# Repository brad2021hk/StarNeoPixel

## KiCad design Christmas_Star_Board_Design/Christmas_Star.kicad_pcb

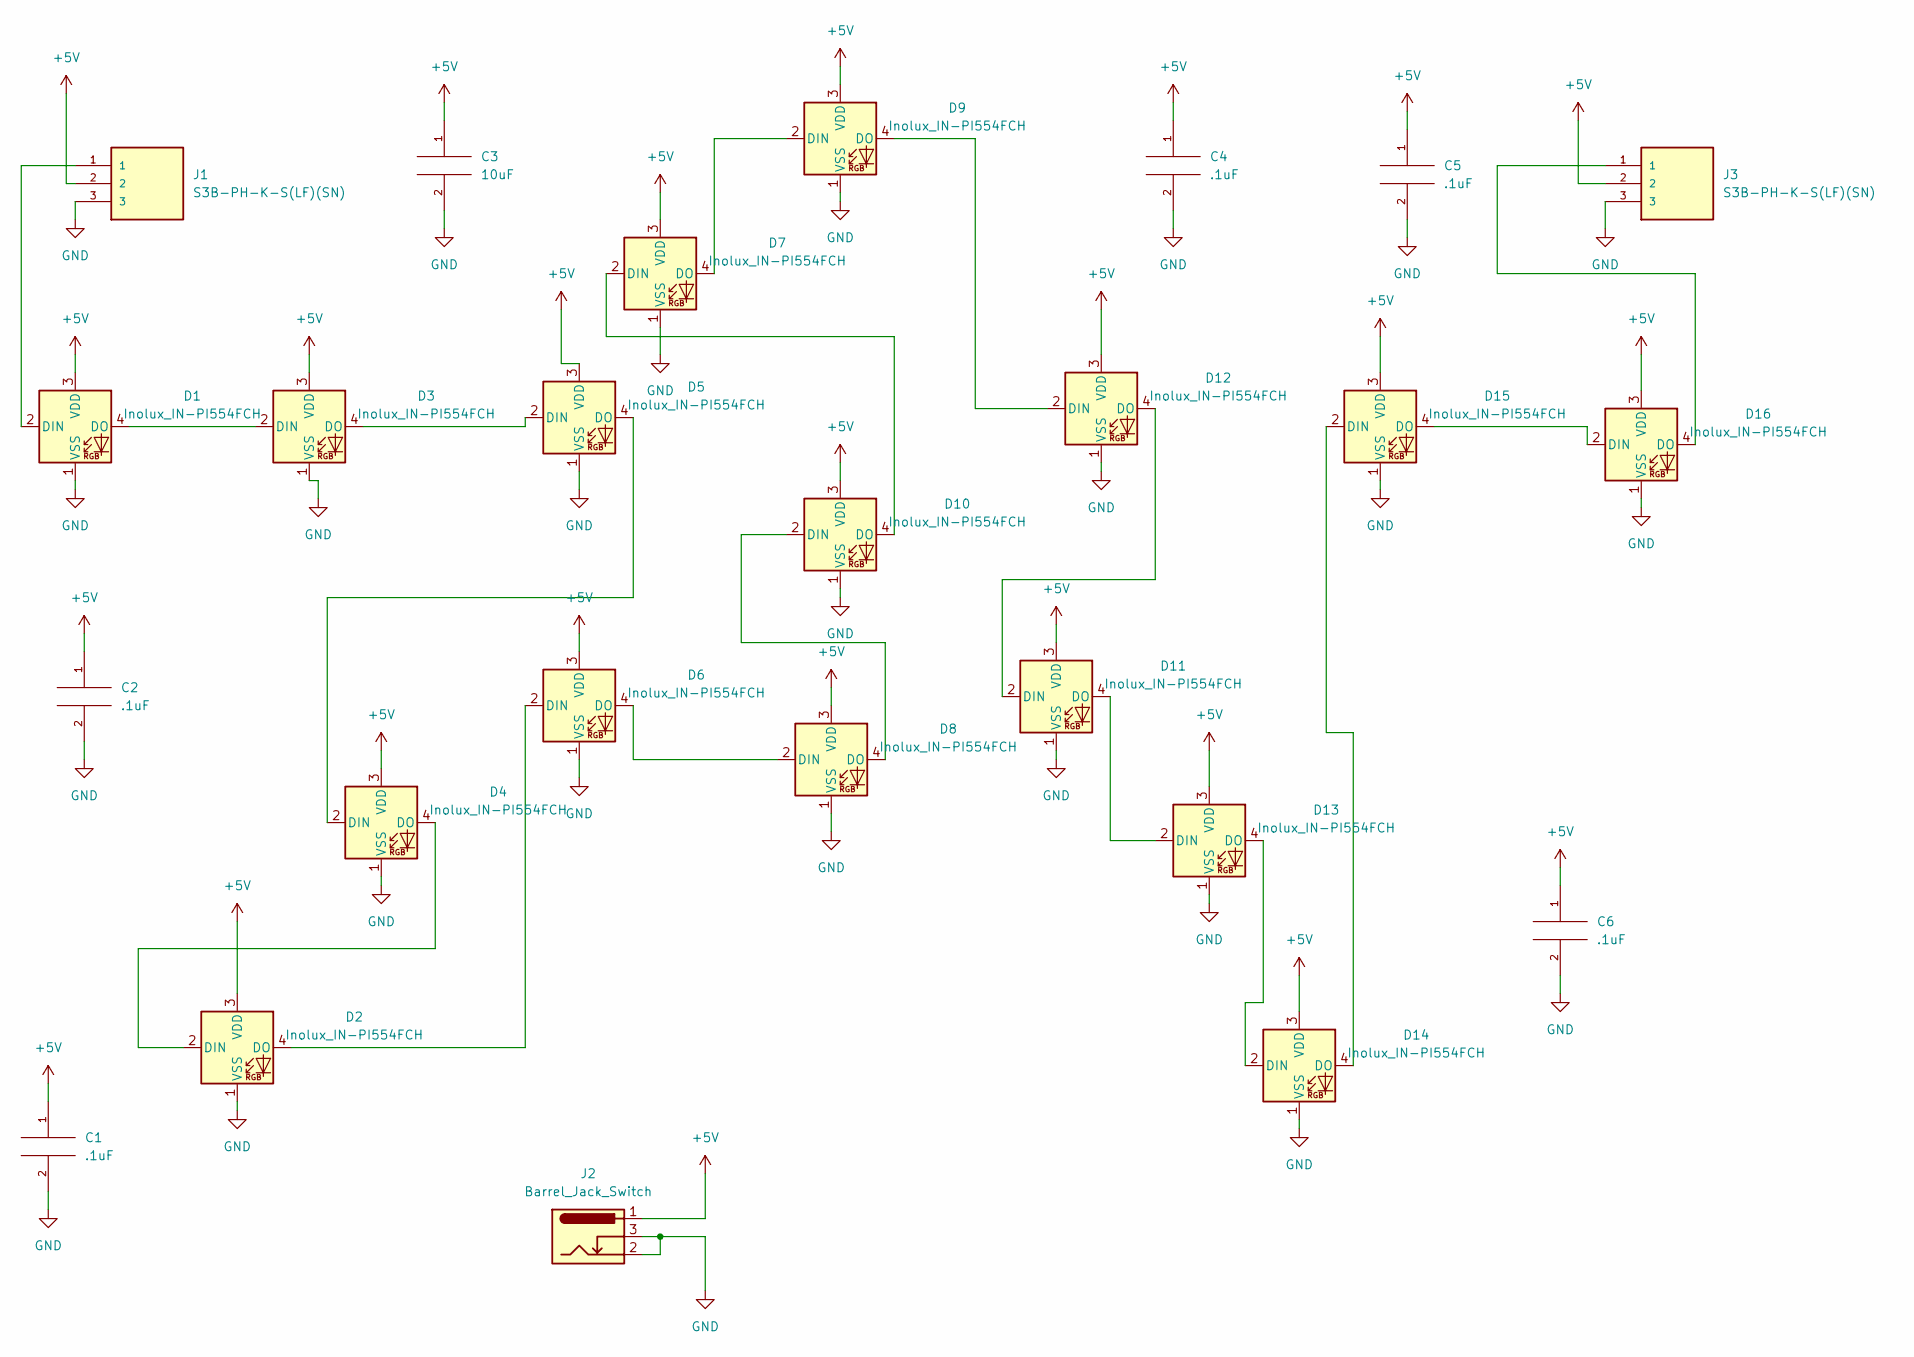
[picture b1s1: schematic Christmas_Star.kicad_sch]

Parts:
C1, C2, C4, C5, C6: .1uF; C_Disc_D3.8mm_W2.6mm_P2.50mm
C3: 10uF; C_Disc_D4.7mm_W2.5mm_P5.00mm
D1, D2, D3, D4, D5, D6, D7, D8, D9, D10, D11, D12, D13, D14, D15, D16: Inolux_IN-PI554FCH; LED_Inolux_IN-PI554FCH_PLCC4_5.0x5.0mm_P3.2mm
J1, J3: S3B-PH-K-S(LF)(SN); JST_S3B-PH-K-S(LF)(SN)
J2: Barrel_Jack_Switch; BarrelJack_CUI_PJ-102AH_Horizontal

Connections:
+5V: C1.1, C2.1, C3.1, C4.1, C5.1, C6.1, D1.3 (VDD), D2.3 (VDD), D3.3 (VDD), D4.3 (VDD), D5.3 (VDD), D6.3 (VDD), D7.3 (VDD), D8.3 (VDD), D9.3 (VDD), D10.3 (VDD), D11.3 (VDD), D12.3 (VDD), D13.3 (VDD), D14.3 (VDD), D15.3 (VDD), D16.3 (VDD), J1.2, J2.1, J3.2
GND: C1.2, C2.2, C3.2, C4.2, C5.2, C6.2, D1.1 (VSS), D2.1 (VSS), D3.1 (VSS), D4.1 (VSS), D5.1 (VSS), D6.1 (VSS), D7.1 (VSS), D8.1 (VSS), D9.1 (VSS), D10.1 (VSS), D11.1 (VSS), D12.1 (VSS), D13.1 (VSS), D14.1 (VSS), D15.1 (VSS), D16.1 (VSS), J1.3, J2.2, J2.3, J3.3
unnamed: D1.2 (DIN), J1.1
unnamed: D2.2 (DIN), D4.4 (DO)
unnamed: D2.4 (DO), D6.2 (DIN)
unnamed: D1.4 (DO), D3.2 (DIN)
unnamed: D3.4 (DO), D5.2 (DIN)
unnamed: D4.2 (DIN), D5.4 (DO)
unnamed: D6.4 (DO), D8.2 (DIN)
unnamed: D8.4 (DO), D10.2 (DIN)
unnamed: D7.4 (DO), D9.2 (DIN)
unnamed: D7.2 (DIN), D10.4 (DO)
unnamed: D11.2 (DIN), D12.4 (DO)
unnamed: D11.4 (DO), D13.2 (DIN)
unnamed: D9.4 (DO), D12.2 (DIN)
unnamed: D13.4 (DO), D14.2 (DIN)
unnamed: D14.4 (DO), D15.2 (DIN)
unnamed: D15.4 (DO), D16.2 (DIN)
unnamed: D16.4 (DO), J3.1

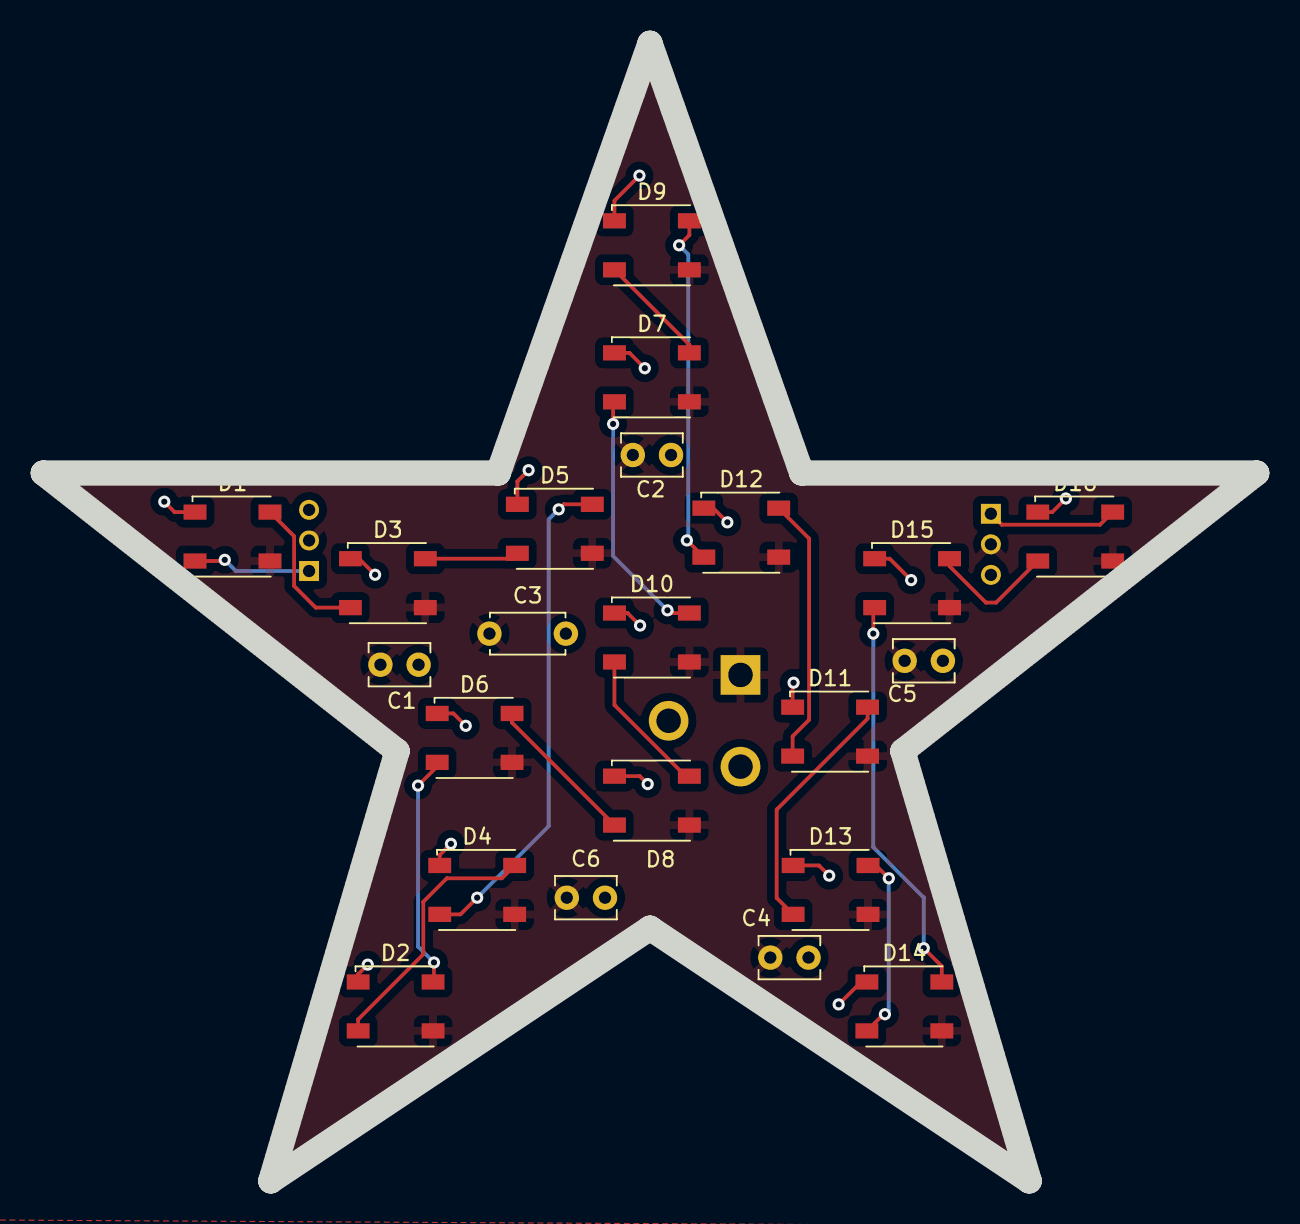
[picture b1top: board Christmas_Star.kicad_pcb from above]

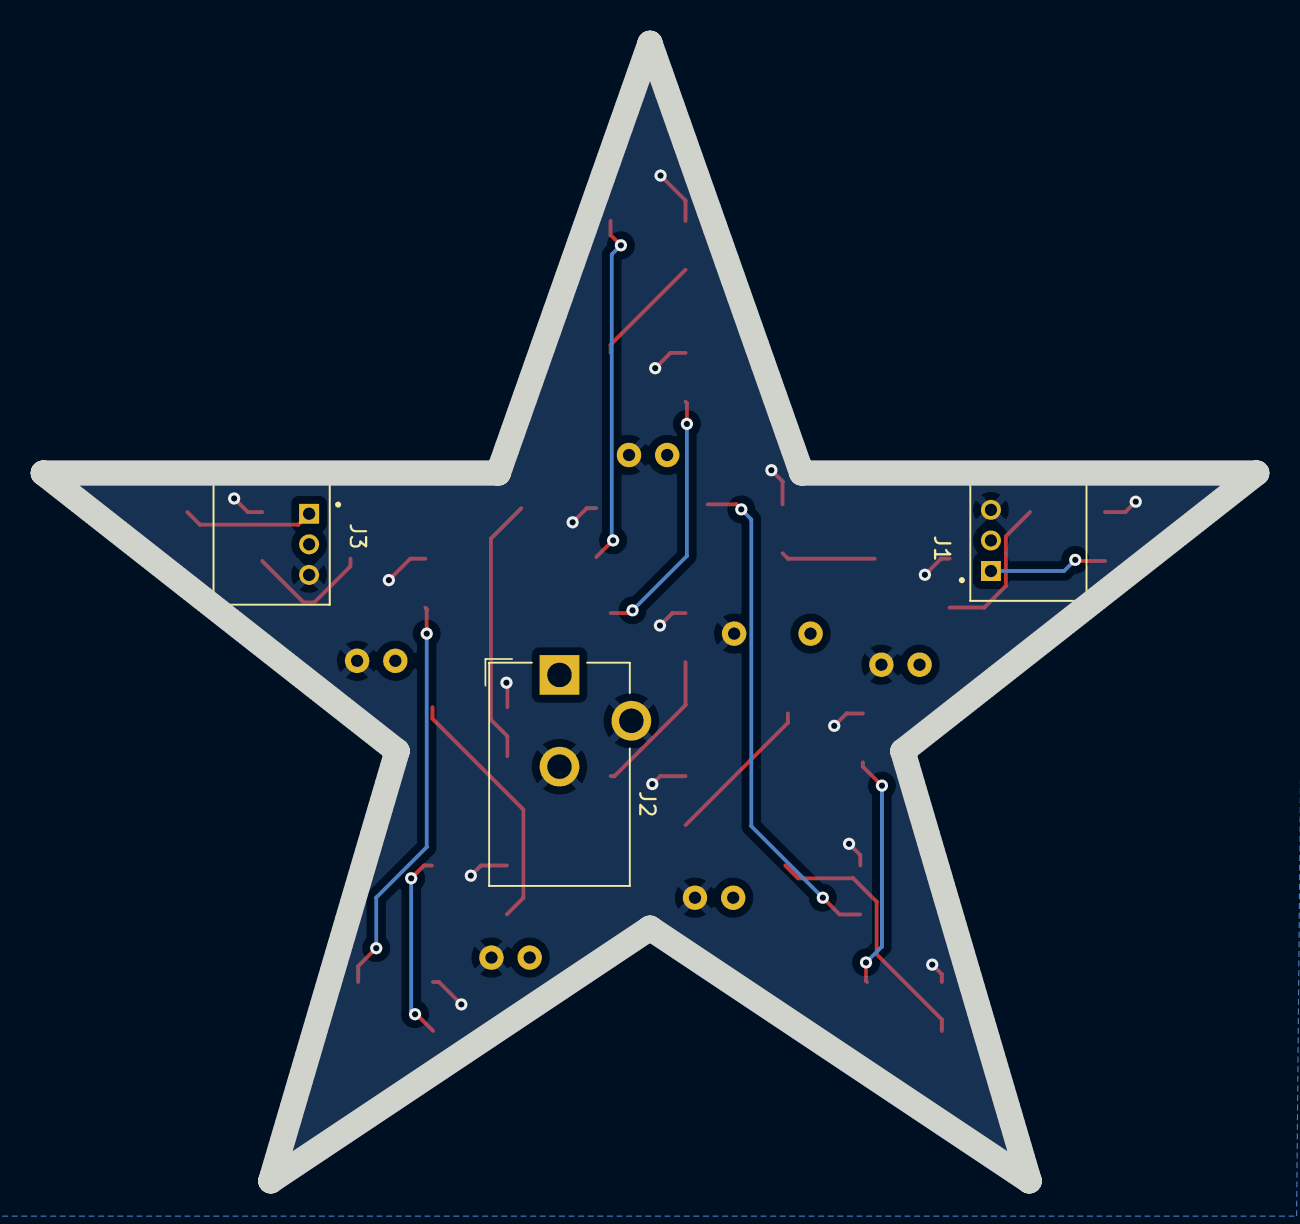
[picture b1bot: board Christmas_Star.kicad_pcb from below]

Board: 2 copper layers, 79.4 x 74.4 mm, 25 parts (3 on the bottom side), 19 nets.

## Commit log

2022-12-18 Initial Commit
    Initial Commit.
2022-12-18 Remove Unused Python Code
    Cleaned up my example code.
